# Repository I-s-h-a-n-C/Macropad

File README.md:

# Macropad
My macropad for HackClub

## **Inspiration**
I tend to use a few shortcuts (namely Ctrl+c, Ctrl+v, Ctrl+s, Ctrl+z) a lot, especially for programming and designing, and I use esc and jump a lot for playing video games. I also prefer a rotary encoder for volume and screen brightness. The problem is that it is less efficient than having a dedicated key for these actions.

## **Challenges**
This was my first time ever using KiCad, and ever designing a PCB! Before this I had only ever used bread boards or protoboards and learning to make PCBs was the main hurdle.

## **Specifications**

### BOM:
* 6x Cherry MX Switches
* 2x SK6812 MINI Leds
* 1x XIAO RP2040
* 4x Blank DSA Keycaps
* 4x M3x16 Bolt
* 4x M3 Heatset
* 2x EC11 Rotary encoders 

### Others:
* KMK Firmware
* Top Case.stl
* Bottom Case.stl

## Schematic

## PCB

## Case

## Build

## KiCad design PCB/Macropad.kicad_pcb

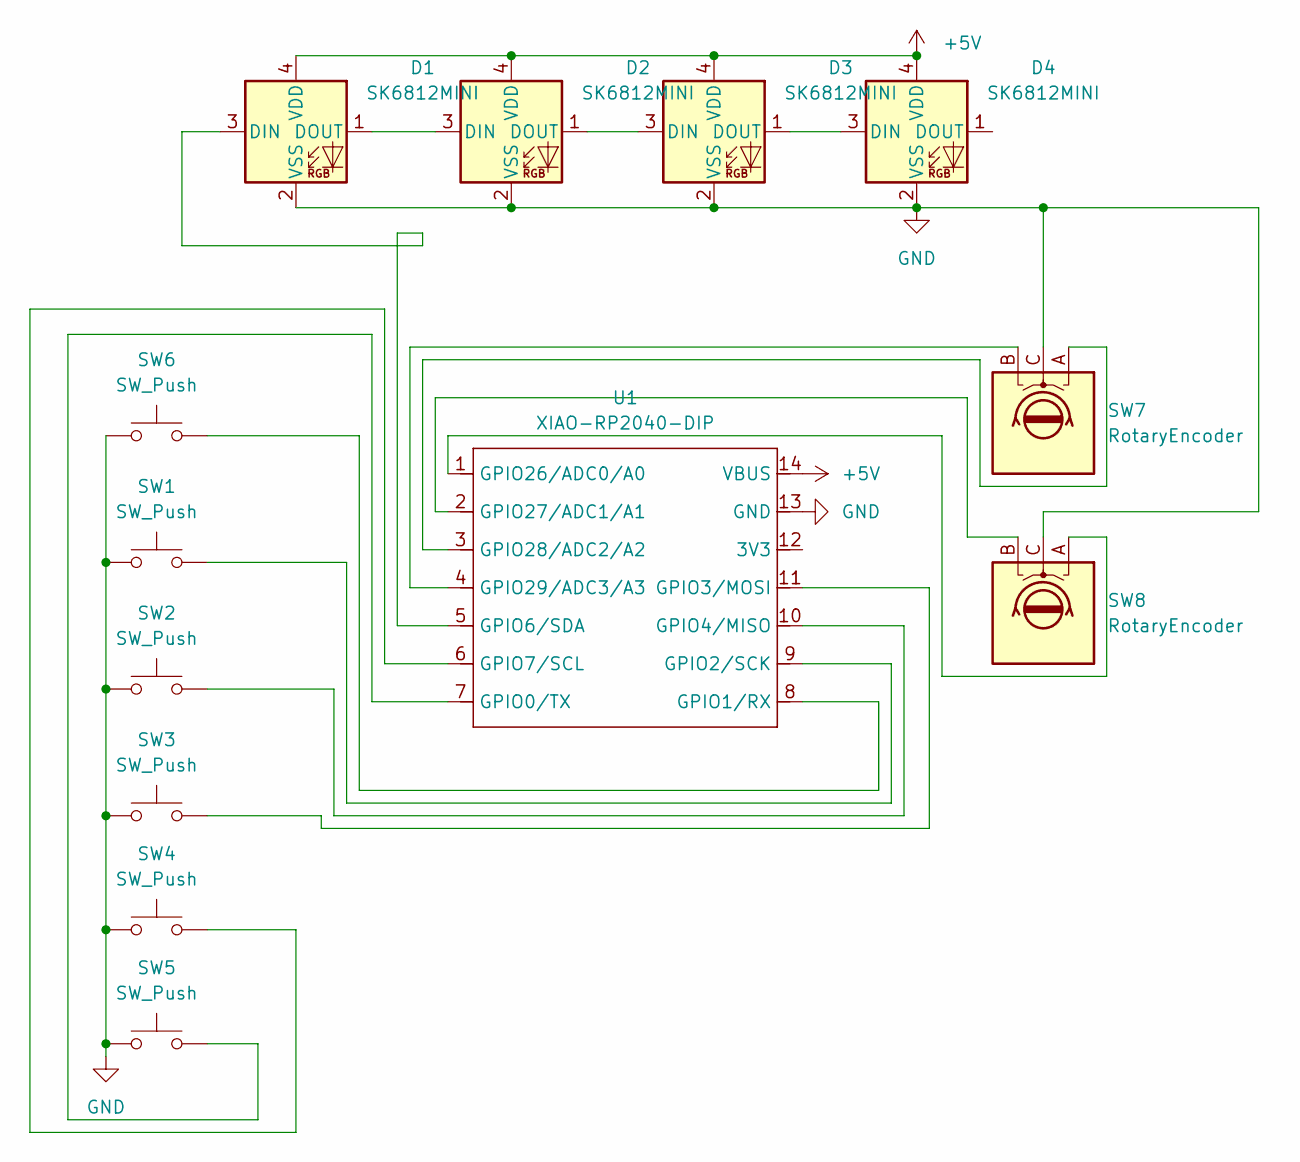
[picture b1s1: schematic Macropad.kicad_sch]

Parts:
D1, D2, D3, D4: SK6812MINI; LED_SK6812MINI_PLCC4_3.5x3.5mm_P1.75mm
SW1, SW2, SW3, SW4, SW5, SW6: SW_Push; SW_Cherry_MX_1.00u_PCB
SW7, SW8: RotaryEncoder; RotaryEncoder_Alps_EC11E_Vertical_H20mm
U1: XIAO-RP2040-DIP

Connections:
+5V: D1.4 (VDD), D2.4 (VDD), D3.4 (VDD), D4.4 (VDD), U1.14 (VBUS)
GND: D1.2 (VSS), D2.2 (VSS), D3.2 (VSS), D4.2 (VSS), SW1.1, SW2.1, SW3.1, SW4.1, SW5.1, SW6.1, SW7.C, SW8.C, U1.13 (GND)
unnamed: D1.3 (DIN), U1.5 (GPIO6/SDA)
unnamed: D1.1 (DOUT), D2.3 (DIN)
unnamed: D2.1 (DOUT), D3.3 (DIN)
unnamed: D3.1 (DOUT), D4.3 (DIN)
unnamed: SW5.2, U1.7 (GPIO0/TX)
unnamed: SW6.2, U1.8 (GPIO1/RX)
unnamed: SW1.2, U1.9 (GPIO2/SCK)
unnamed: SW3.2, U1.11 (GPIO3/MOSI)
unnamed: SW2.2, U1.10 (GPIO4/MISO)
unnamed: SW4.2, U1.6 (GPIO7/SCL)
unnamed: SW8.A, U1.1 (GPIO26/ADC0/A0)
unnamed: SW8.B, U1.2 (GPIO27/ADC1/A1)
unnamed: SW7.A, U1.3 (GPIO28/ADC2/A2)
unnamed: SW7.B, U1.4 (GPIO29/ADC3/A3)

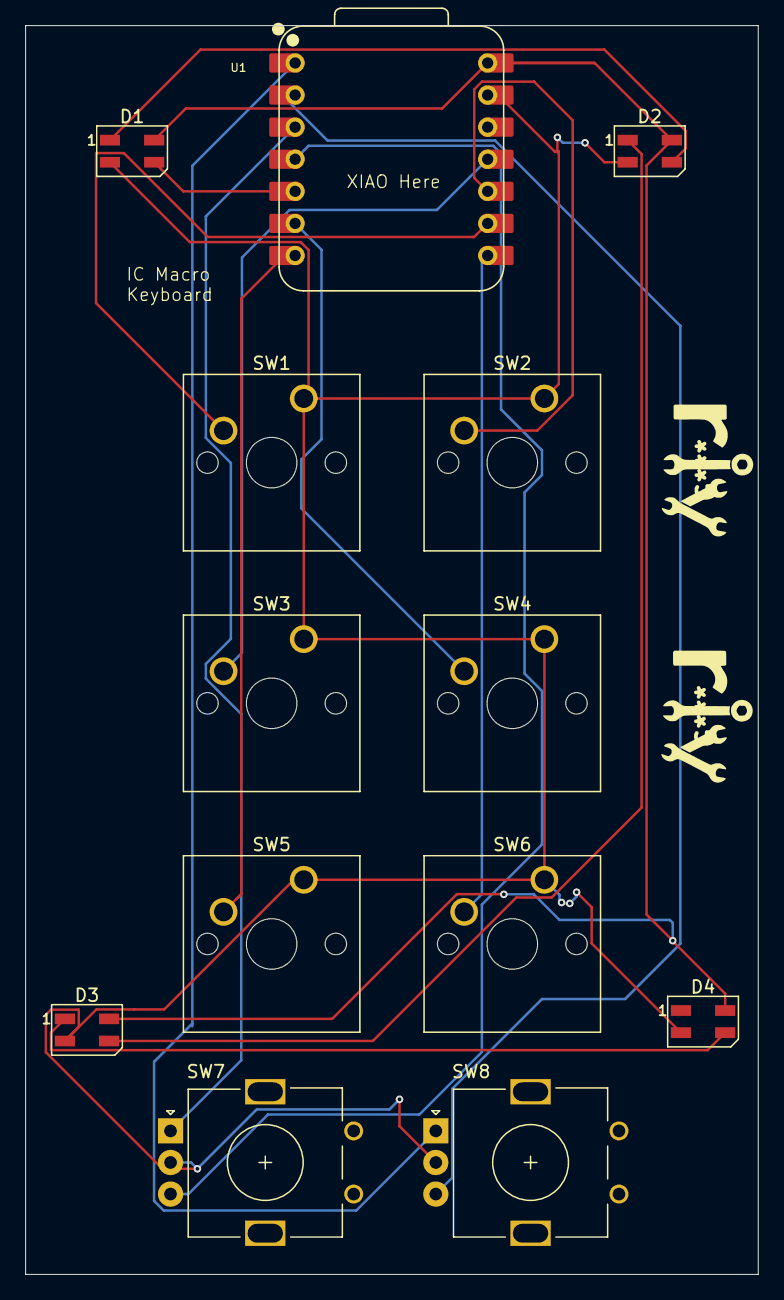
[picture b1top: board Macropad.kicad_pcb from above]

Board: 2 copper layers, 58.0 x 98.9 mm, 13 parts (0 on the bottom side), 16 nets.

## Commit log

2025-11-30 Expand README with detailed project information
    Added sections for inspiration, challenges, specifications, schematic, PCB, and case with images.
2025-12-01 submission
2025-12-01 edited
    edited
2025-12-01 Replace images in README with updated versions
    Updated schematic and PCB images in the README.
2025-12-01 submit
    submit
2025-12-01 Update PCB image in README.md
    Replaced PCB image in README with a new image.
2025-12-02 submit
2025-12-26 Updated Macropad Step with new Case
